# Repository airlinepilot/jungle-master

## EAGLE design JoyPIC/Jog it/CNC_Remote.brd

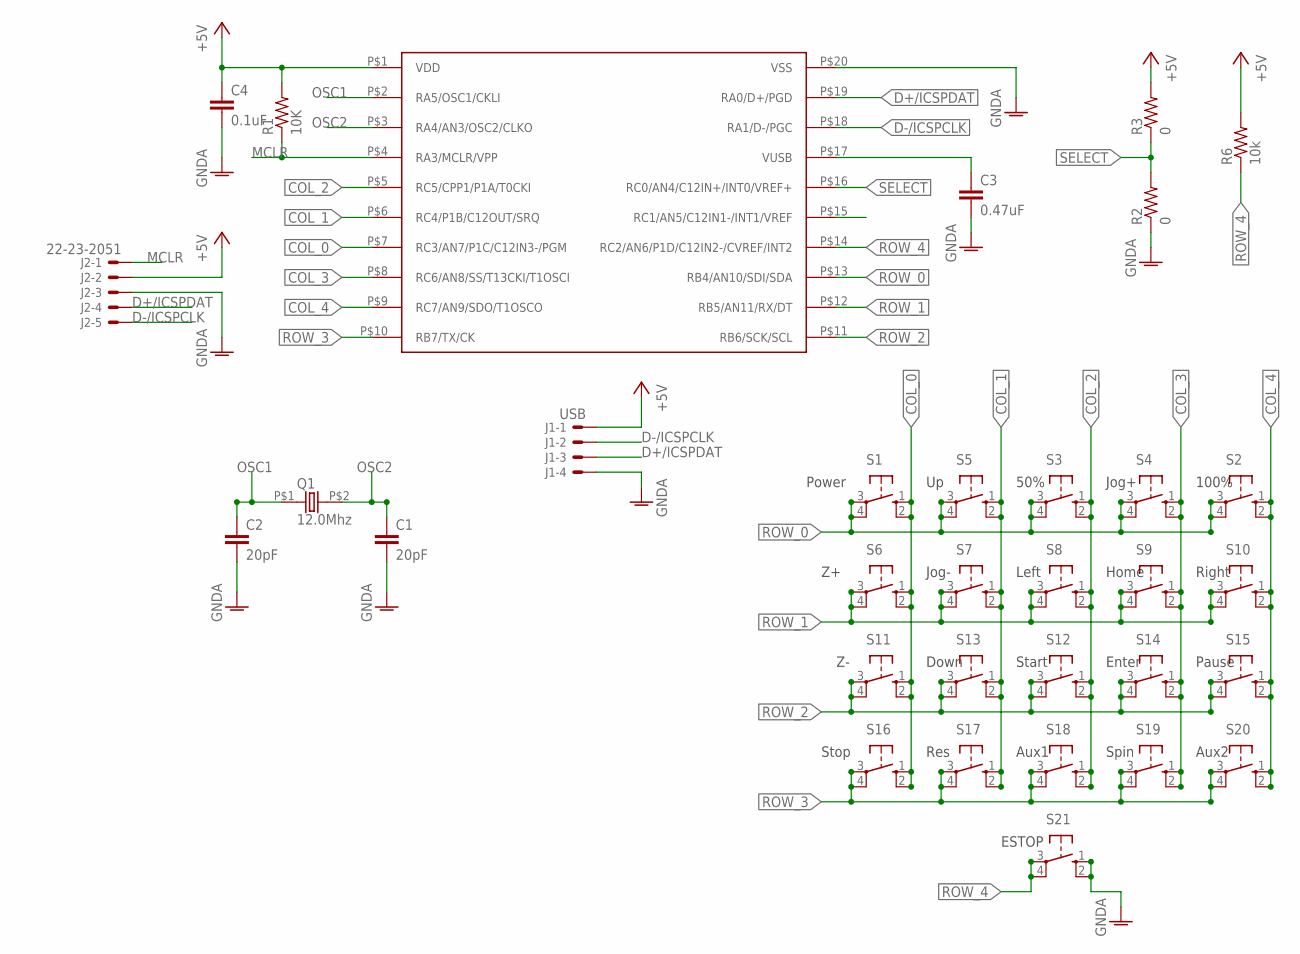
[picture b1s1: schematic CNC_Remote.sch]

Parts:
C1, C2: 20pF; C0603
C3: 0.47uF; C0603
C4: 0.1uF; C0603
J1: USB; 22-23-2041
J2: 22-23-2051
Q1: 12.0Mhz; HC49/US
R1: 10K; R0603
R2, R3: 0; R0603
R6: 10k; R0603
S1, S2, S3, S4, S5, S6, S7, S8, S9, S10, S11, S12, S13, S14, S15, S16, S17, S18, S19, S20, S21: 10-XX; B3F-10XX
U1: PIC18F1K50SOIC; SOIC-20

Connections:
+5V: C4.1, J1.1, J2.2, R1.2, R3.2, R6.2, U1.P$1 (VDD)
COL_0: S1.1 (S), S1.2 (S1), S6.1 (S), S6.2 (S1), S11.1 (S), S11.2 (S1), S16.1 (S), S16.2 (S1), U1.P$7 (RC3/AN7/P1C/C12IN3-/PGM)
COL_1: S5.1 (S), S5.2 (S1), S7.1 (S), S7.2 (S1), S13.1 (S), S13.2 (S1), S17.1 (S), S17.2 (S1), U1.P$6 (RC4/P1B/C12OUT/SRQ)
COL_2: S3.1 (S), S3.2 (S1), S8.1 (S), S8.2 (S1), S12.1 (S), S12.2 (S1), S18.1 (S), S18.2 (S1), U1.P$5 (RC5/CPP1/P1A/T0CKI)
COL_3: S4.1 (S), S4.2 (S1), S9.1 (S), S9.2 (S1), S14.1 (S), S14.2 (S1), S19.1 (S), S19.2 (S1), U1.P$8 (RC6/AN8/SS/T13CKI/T1OSCI)
COL_4: S2.1 (S), S2.2 (S1), S10.1 (S), S10.2 (S1), S15.1 (S), S15.2 (S1), S20.1 (S), S20.2 (S1), U1.P$9 (RC7/AN9/SDO/T1OSCO)
D+/ICSPDAT: J1.3, J2.4, U1.P$19 (RA0/D+/PGD)
D-/ICSPCLK: J1.2, J2.5, U1.P$18 (RA1/D-/PGC)
GNDA: C1.2, C2.2, C3.2, C4.2, J1.4, J2.3, R2.1, S21.1 (S), S21.2 (S1), U1.P$20 (VSS)
MCLR: J2.1, R1.1, U1.P$4 (RA3/MCLR/VPP)
unnamed: C3.1, U1.P$17 (VUSB)
OSC1: C2.1, Q1.P$1 (1), U1.P$2 (RA5/OSC1/CKLI)
OSC2: C1.1, Q1.P$2 (2), U1.P$3 (RA4/AN3/OSC2/CLKO)
ROW_0: S1.3, S1.4 (P1), S2.3, S2.4 (P1), S3.3, S3.4 (P1), S4.3, S4.4 (P1), S5.3, S5.4 (P1), U1.P$13 (RB4/AN10/SDI/SDA)
ROW_1: S6.3, S6.4 (P1), S7.3, S7.4 (P1), S8.3, S8.4 (P1), S9.3, S9.4 (P1), S10.3, S10.4 (P1), U1.P$12 (RB5/AN11/RX/DT)
ROW_2: S11.3, S11.4 (P1), S12.3, S12.4 (P1), S13.3, S13.4 (P1), S14.3, S14.4 (P1), S15.3, S15.4 (P1), U1.P$11 (RB6/SCK/SCL)
ROW_3: S16.3, S16.4 (P1), S17.3, S17.4 (P1), S18.3, S18.4 (P1), S19.3, S19.4 (P1), S20.3, S20.4 (P1), U1.P$10 (RB7/TX/CK)
ROW_4: R6.1, S21.3, S21.4 (P1), U1.P$14 (RC2/AN6/P1D/C12IN2-/CVREF/INT2)
SELECT: R2.2, R3.1, U1.P$16 (RC0/AN4/C12IN+/INT0/VREF+)

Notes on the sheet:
Power
100%
50%
Jog+
Jog-
Left
Home
Right
Start
Down
Enter
Pause
Stop
Res
Aux1
Spin
Aux2
ESTOP

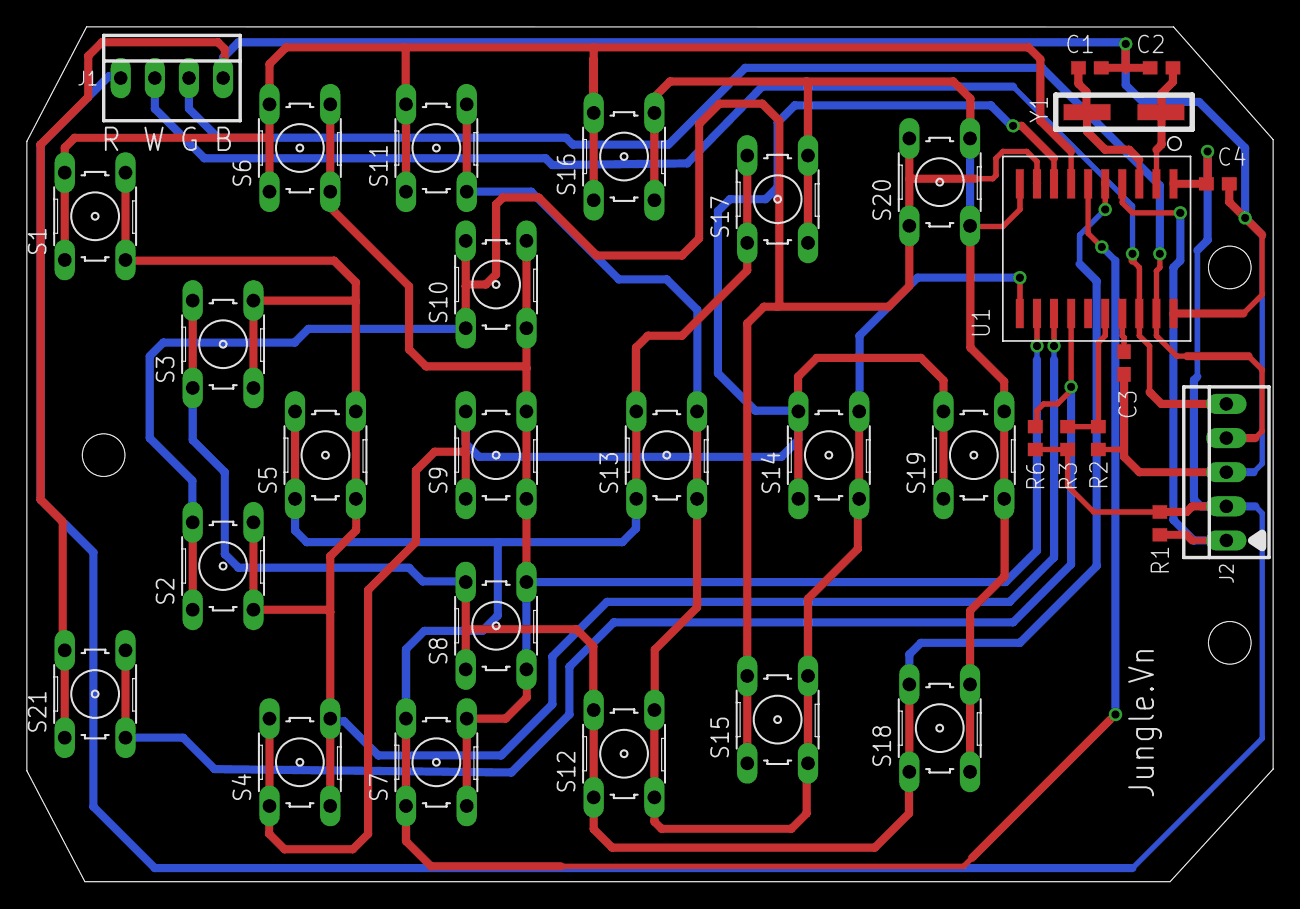
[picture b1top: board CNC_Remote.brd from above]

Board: 2 copper layers, 92.8 x 63.6 mm, 33 parts (0 on the bottom side), 19 nets.

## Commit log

2016-06-23 LinuxCNC + BBB
    Jungle BBB Cape 6-Axis, 4Ch A/D
2016-06-23 Readme
    Added Readme file
2016-06-23 Ready Update
    Need to add LinuxCNC Debug
2016-06-24 Jungle-Notes
    MQTT - Failed to start after server restart
2016-06-24 AlaMode-V3.0
    3DPrinter cape
